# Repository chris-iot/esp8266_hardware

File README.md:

# esp8266_hardware
All layouts and schematics for my ESP8266 based home automation solution

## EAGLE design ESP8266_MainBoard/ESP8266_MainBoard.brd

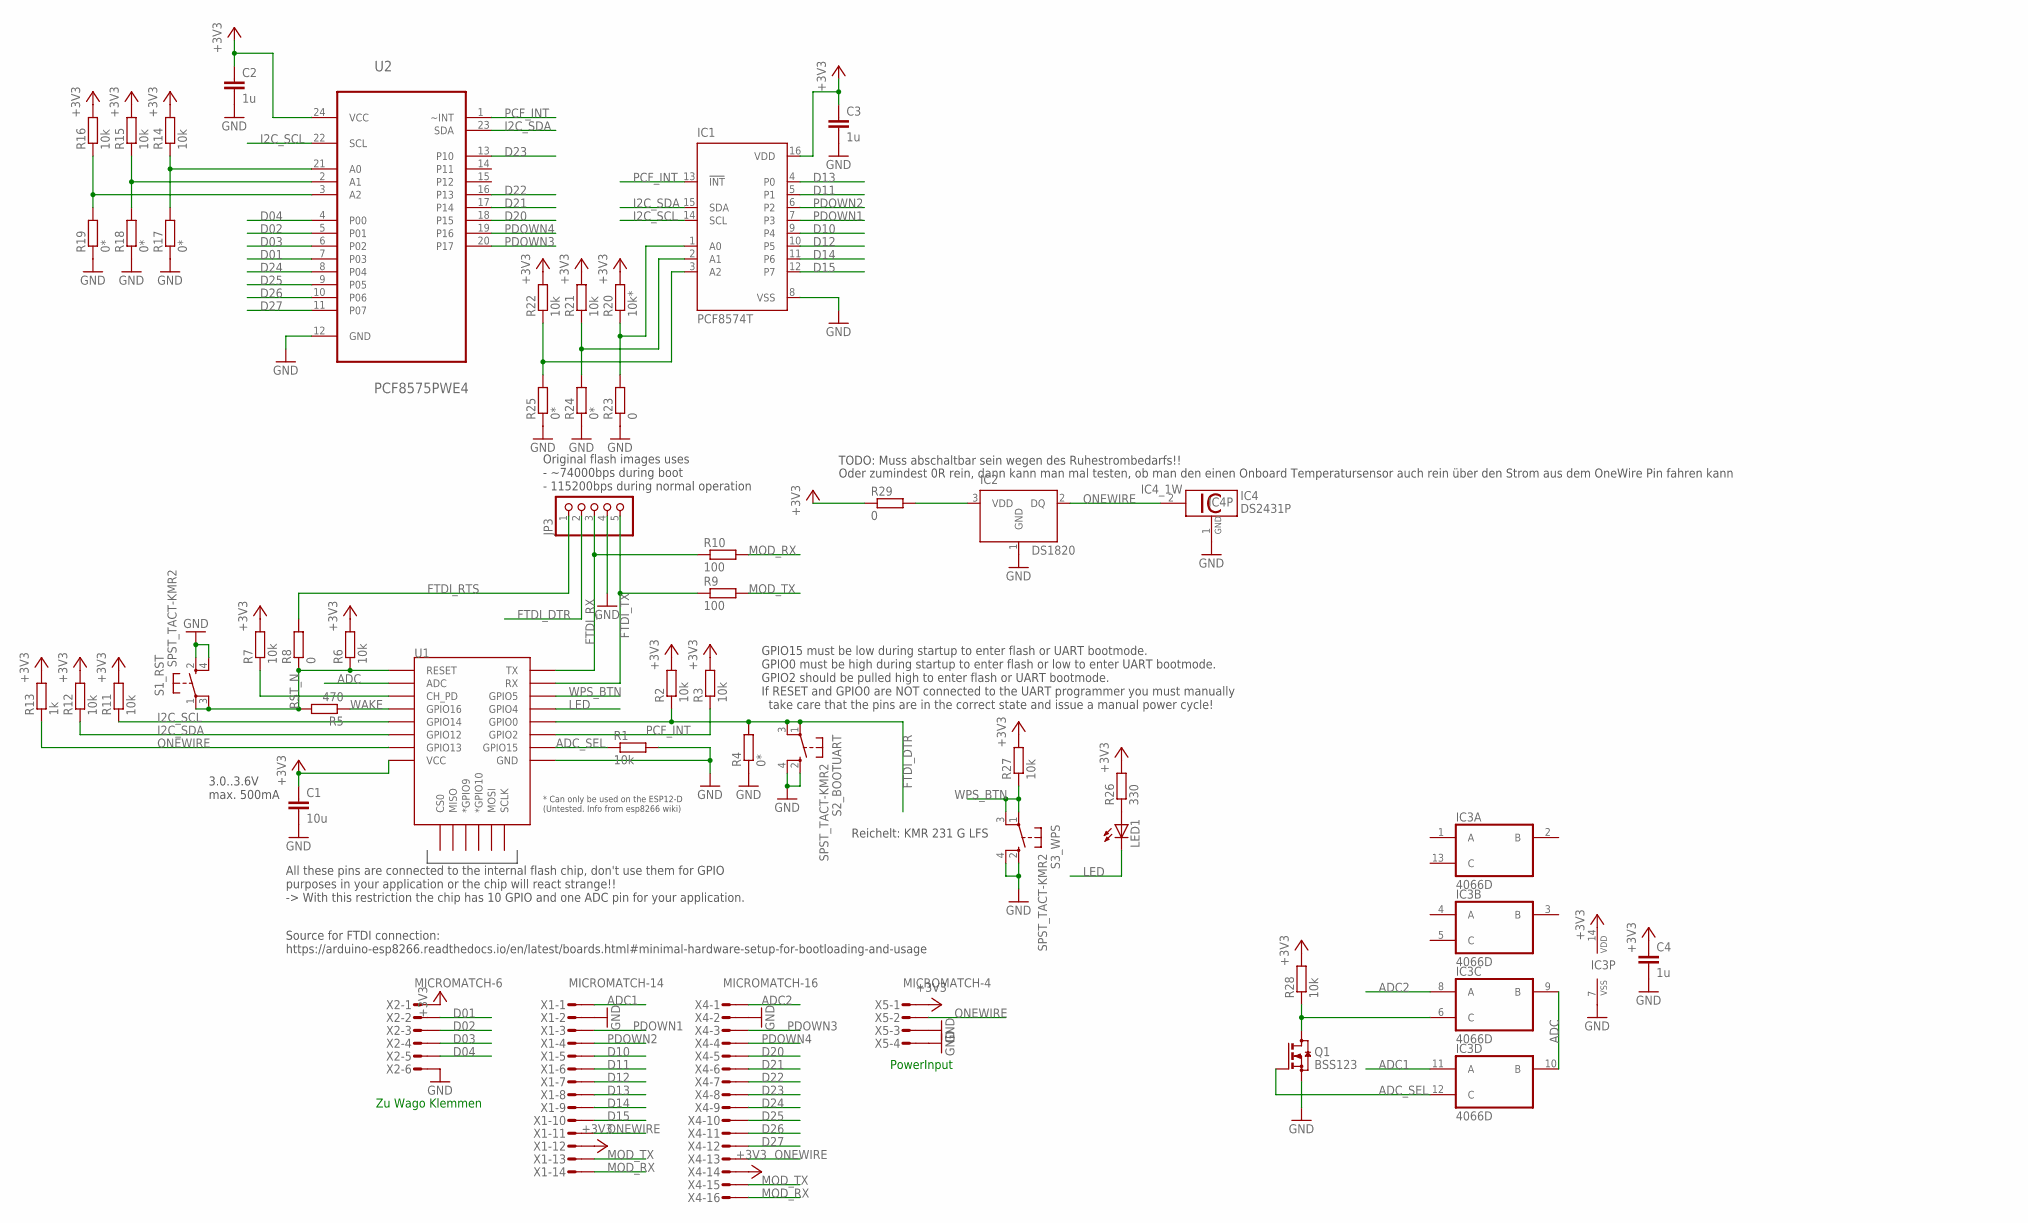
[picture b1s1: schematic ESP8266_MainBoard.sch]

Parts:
C1: 10u; C0805
C2, C3, C4: 1u; C0402
IC1: PCF8574T; SO16W
IC2: DS1820; TO-92
IC3: 4066D; SO14
IC4: DS2431P; TSOC6
JP3: PINHD-1X5; 1X05
LED1: LEDCHIP-LED0603; CHIP-LED0603
Q1: BSS123; SOT23
R1, R2, R3, R6, R7, R11, R12, R14, R15, R16, R21, R22, R27, R28: 10k; R0402
R4, R17, R18, R19, R24, R25: 0*; R0402
R5: 470; R0402
R8, R23, R29: 0; R0402
R9, R10: 100; R0402
R13: 1k; R0402
R20: 10k*; R0402
R26: 330; R0402
S1_RST, S2_BOOTUART, S3_WPS: SPST_TACT-KMR2; KMR2
U1: ESP12ESMD; ESP12E-SMD
U2: PCF8575PWE4; SOP65P640X120-24N
X1: MICROMATCH-14
X2: MICROMATCH-6
X4: MICROMATCH-16
X5: MICROMATCH-4

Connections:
+3V3: C1.1, C2.1, C3.1, C4.1, IC1.16 (VDD), IC3.14 (VDD), R2.2, R3.2, R6.2, R7.2, R11.2, R12.2, R13.2, R14.2, R15.2, R16.2, R20.2, R21.2, R22.2, R26.2, R27.2, R28.2, R29.1, U1.VCC, U2.24 (VCC), X1.12, X2.1, X4.14, X5.1
ADC: IC3.9 (B), IC3.10 (B), U1.ADC
ADC1: IC3.11 (A), X1.1
ADC2: IC3.8 (A), X4.1
ADC_SEL: IC3.12 (C), Q1.1 (G), R1.1, U1.GPIO15
D01: U2.7 (P03), X2.2
D02: U2.5 (P01), X2.3
D03: U2.6 (P02), X2.4
D04: U2.4 (P00), X2.5
D10: IC1.9 (P4), X1.5
D11: IC1.5 (P1), X1.6
D12: IC1.10 (P5), X1.7
D13: IC1.4 (P0), X1.8
D14: IC1.11 (P6), X1.9
D15: IC1.12 (P7), X1.10
D20: U2.18 (P15), X4.5
D21: U2.17 (P14), X4.6
D22: U2.16 (P13), X4.7
D23: U2.13 (P10), X4.8
D24: U2.8 (P04), X4.9
D25: U2.9 (P05), X4.10
D26: U2.10 (P06), X4.11
D27: U2.11 (P07), X4.12
FTDI_DTR: JP3.2, R2.1, R4.2, S2_BOOTUART.1, S2_BOOTUART.3 (P1), U1.GPIO0
FTDI_RTS: JP3.1, R8.2
FTDI_RX: JP3.3, R10.1, U1.TXD0 (TX)
FTDI_TX: JP3.5, R9.1, U1.RXD0 (RX)
GND: C1.2, C2.2, C3.2, C4.2, IC1.8 (VSS), IC2.1 (GND), IC3.7 (VSS), IC4.1 (GND), JP3.4, Q1.2 (S), R1.2, R4.1, R17.1, R18.1, R19.1, R23.1, R24.1, R25.1, S1_RST.2 (S), S1_RST.4 (S1), S2_BOOTUART.2 (S), S2_BOOTUART.4 (S1), S3_WPS.2 (S), S3_WPS.4 (S1), U1.GND, U2.12 (GND), X1.2, X2.6, X4.2, X5.3, X5.4
I2C_SCL: IC1.14 (SCL), R11.1, U1.GPIO14, U2.22 (SCL)
I2C_SDA: IC1.15 (SDA), R12.1, U1.GPIO12, U2.23 (SDA)
LED: LED1.C, U1.GPIO4
MOD_RX: R10.2, X1.14, X4.16
MOD_TX: R9.2, X1.13, X4.15
unnamed: IC3.6 (C), Q1.3 (D), R28.1
unnamed: R14.1, R17.2, U2.21 (A0)
unnamed: R15.1, R18.2, U2.2 (A1)
unnamed: R7.1, U1.CH_PD
unnamed: IC2.3 (VDD), R29.2
unnamed: R16.1, R19.2, U2.3 (A2)
unnamed: IC1.1 (A0), R20.1, R23.2
unnamed: IC1.2 (A1), R21.1, R24.2
unnamed: IC1.3 (A2), R22.1, R25.2
unnamed: LED1.A, R26.1
ONEWIRE: IC2.2 (DQ), IC4.2 (1W), R13.1, U1.GPIO13, X1.11, X4.13, X5.2
PCF_INT: IC1.13 (!INT), R3.1, U1.GPIO2, U2.1 (~INT)
PDOWN1: IC1.7 (P3), X1.3
PDOWN2: IC1.6 (P2), X1.4
PDOWN3: U2.20 (P17), X4.3
PDOWN4: U2.19 (P16), X4.4
RST_N: R5.2, R6.1, R8.1, S1_RST.1, S1_RST.3 (P1), U1.RESET
WAKE: R5.1, U1.GPIO16
WPS_BTN: R27.1, S3_WPS.1, S3_WPS.3 (P1), U1.GPIO5

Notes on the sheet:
3.0..3.6V max. 500mA
GPIO15 must be low during startup to enter flash or UART bootmode. GPIO0 must be high during startup to enter flash or low to enter UART bootmode. GPIO2 should be pulled high to enter flash or UART bootmode. If RESET and GPIO0 are NOT connected to the UART programmer you must manually take care tha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
All these pins are connected to the internal flash chip, don't use them for GPIO purposes in your application or the chip will react strange!! -> With this restriction the chip has 10 GPIO and one ADC pin for your application.
Original flash images uses - ~74000bps during boot - 115200bps during normal operation
Source for FTDI connection: https://arduino-esp8266.readthedocs.io/en/latest/boards.html#minimal-hardware-setup-for-bootloading-and-usage
Zu Wago Klemmen
PowerInput
Reichelt: KMR 231 G LFS
TODO: Muss abschaltbar sein wegen des Ruhestrombedarfs!!
Oder zumindest 0R rein, dann kann man mal testen, ob man den einen Onboard Temperatursensor auch rein über den Strom aus dem OneWire Pin fahren kann

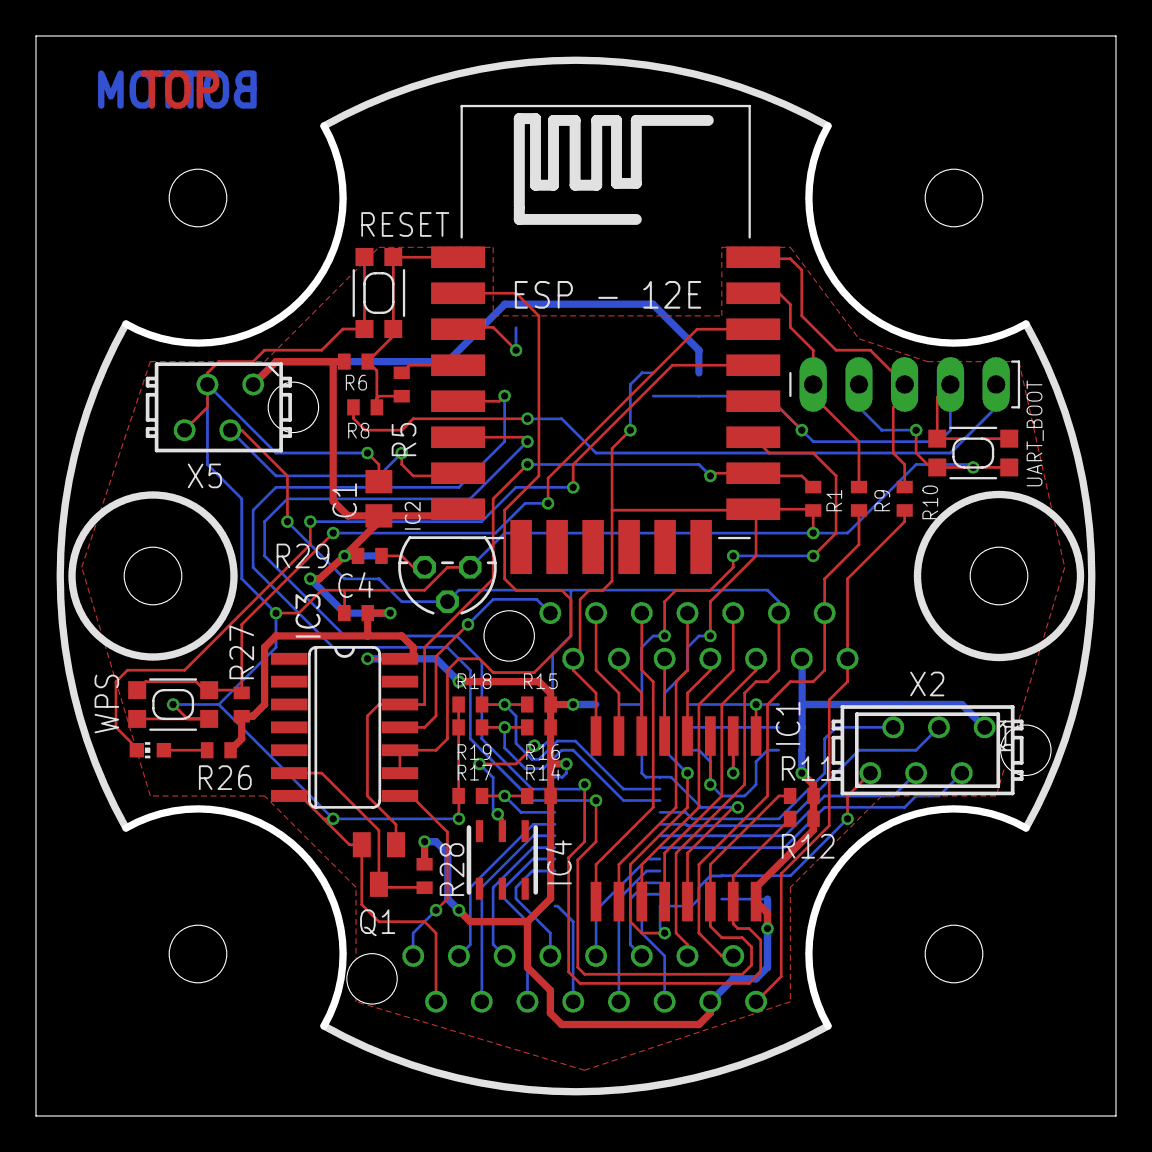
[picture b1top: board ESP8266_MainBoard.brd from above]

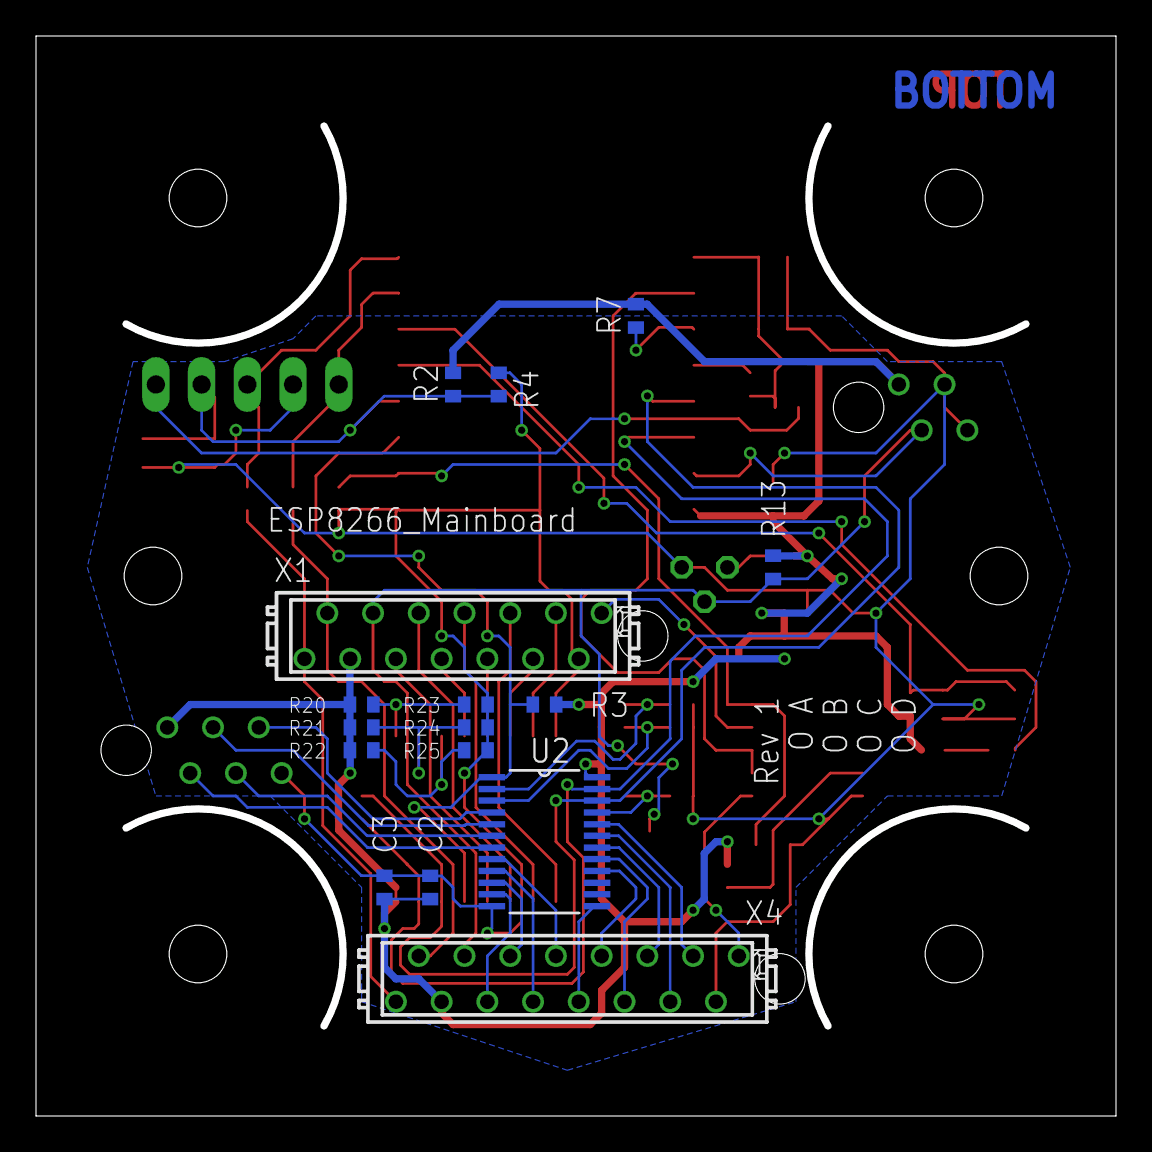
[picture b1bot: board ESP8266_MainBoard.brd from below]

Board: 2 copper layers, 60.0 x 60.0 mm, 49 parts (16 on the bottom side), 52 nets.

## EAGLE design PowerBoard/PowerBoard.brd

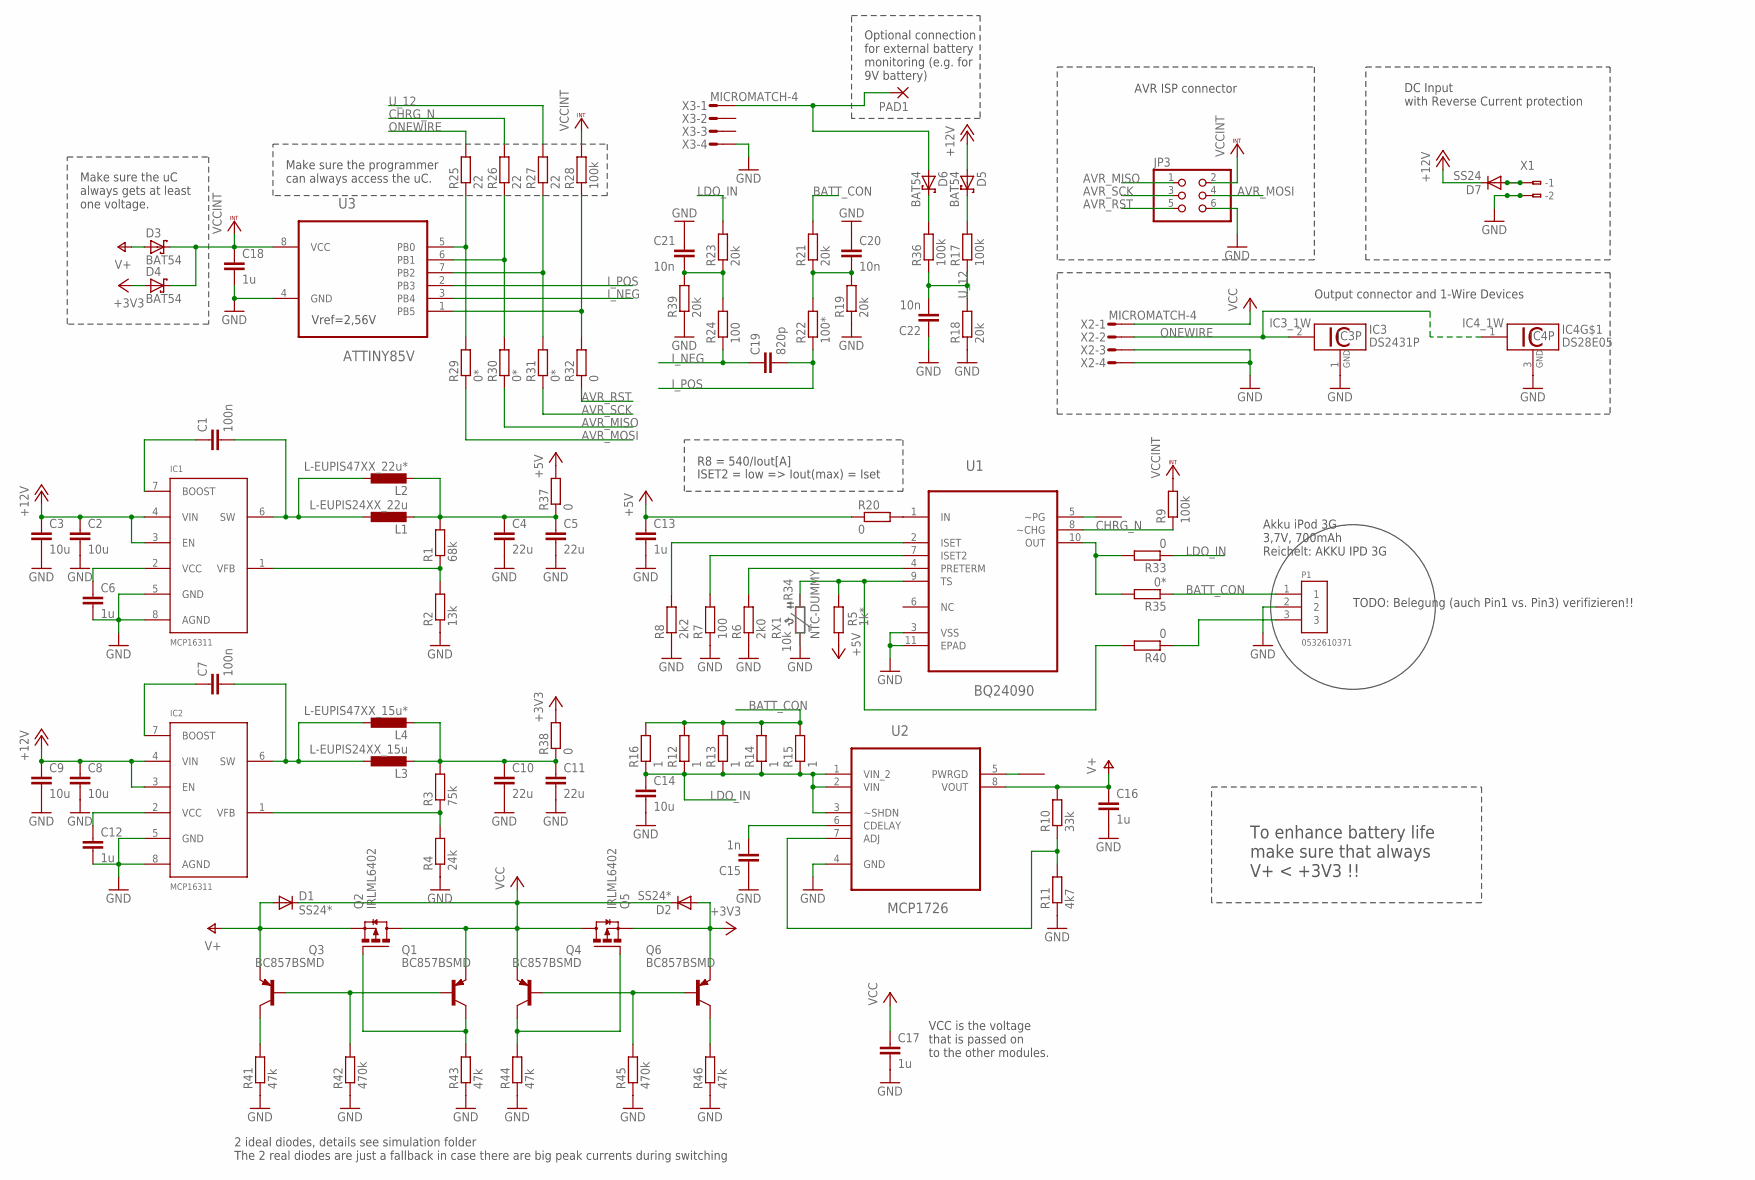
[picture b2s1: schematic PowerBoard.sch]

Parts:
C1, C7: 100n; C0603
C2, C3, C8, C9, C14: 10u; C1210
C4, C5, C10, C11: 22u; C1210
C6, C12, C13, C16, C17, C18: 1u; C0603
C15: 1n; C0603
C19: 820p; C0603
C20, C21, C22: 10n; C0603
D1, D2: SS24*; SMB
D3, D4, D5, D6: BAT54; SOT23
D7: SS24; SMB
IC1, IC2: MCP16311; SOP65P490X110-8N
IC3: DS2431P; TSOC6
IC4: DS28E05; SOT23
JP3: PINHD-2X3; 2X03
L1: L-EUPIS24XX_22u; PIS24XX
L2: L-EUPIS47XX_22u*; PIS47XX
L3: L-EUPIS24XX_15u; PIS24XX
L4: L-EUPIS47XX_15u*; PIS47XX
P1: 0532610371; MOLEX_0532610371
PAD1: WIREPADSMD2,54-5,08; SMD2,54-5,08
Q1, Q3, Q4, Q6: BC857BSMD; SOT23-BEC
Q2, Q5: IRLML6402; SOT23
R1: 68k; R0603
R2: 13k; R0603
R3: 75k; R0603
R4: 24k; R0603
R5: 1k*; R0603
R6: 2k0; R0603
R7, R24: 100; R0603
R8: 2k2; R0603
R9, R17, R36: 100k; R0603
R10: 33k; R0603
R11: 4k7; R0603
R12, R13, R14, R15, R16: 1; R0402
R18, R19, R21, R23, R39: 20k; R0603
R20, R33, R37, R38, R40: 0; R0603
R22: 100*; R0603
R25, R26, R27: 22; R0402
R28: 100k; R0402
R29, R30, R31: 0*; R0402
R32: 0; R0402
R34: 10k; R0603
R35: 0*; R0603
R41, R43, R44, R46: 47k; R0603
R42, R45: 470k; R0603
U1: BQ24090; SOP50P490X110-11N
U2: MCP1726; SOIC127P490X175-8N
U3: ATTINY85V; SOIC127P798X216-8N
U$1, U$3: PAD100-RND; PAD-100-RND
X1: 233-102
X2, X3: MICROMATCH-4

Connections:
+3V3: D2.A, D4.1 (A), Q5.2 (S), Q6.E, R38.2
+5V: C13.1, R5.1, R20.1, R37.2
+12V: C2.1, C3.1, C8.1, C9.1, D5.1 (A), D7.C, IC1.3 (EN), IC1.4 (VIN), IC2.3 (EN), IC2.4 (VIN)
AVR_MISO: JP3.1, R30.1
AVR_MOSI: JP3.4, R29.1
AVR_RST: JP3.5, R32.1
AVR_SCK: JP3.3, R31.1
BATT_CON: P1.1, R12.2, R13.2, R14.2, R15.2, R16.2, R21.2, R35.1
CHRG_N: R9.1, R26.2, U1.8 (~CHG)
GND: C2.2, C3.2, C4.2, C5.2, C6.2, C8.2, C9.2, C10.2, C11.2, C12.2, C13.2, C14.2, C15.1, C16.2, C17.2, C18.2, C20.1, C21.1, C22.1, IC1.5 (GND), IC1.8 (AGND), IC2.5 (GND), IC2.8 (AGND), IC3.1 (GND), IC4.3 (GND), JP3.6, P1.2, R2.1, R4.1, R6.1, R7.1, R8.1, R11.1, R18.1, R19.1, R34.1, R39.1, R41.1, R42.1, R43.1, R44.1, R45.1, R46.1, U1.3 (VSS), U1.11 (EPAD), U2.4 (GND), U3.4 (GND), X1.A2 (-2), X1.B2 (B-2), X2.3, X2.4, X3.4
I_NEG: C19.1, R24.1, U3.3 (PB4)
I_POS: C19.2, R22.1, U3.2 (PB3)
LDO_IN: C14.1, R12.1, R13.1, R14.1, R15.1, R16.1, R23.2, R33.1, U2.1 (VIN_2), U2.2 (VIN), U2.3 (~SHDN)
unnamed: C1.1, IC1.7 (BOOST)
unnamed: C1.2, IC1.6 (SW), L1.2 (1), L2.2 (1)
unnamed: U2.5 (PWRGD), U$3.P$1
unnamed: R8.2, U1.2 (ISET)
unnamed: IC1.1 (VFB), R1.1, R2.2
unnamed: R7.2, U1.7 (ISET2)
unnamed: C6.1, IC1.2 (VCC)
unnamed: R6.2, U1.4 (PRETERM)
unnamed: C7.1, IC2.7 (BOOST)
unnamed: C7.2, IC2.6 (SW), L3.2 (1), L4.2 (1)
unnamed: IC2.1 (VFB), R3.1, R4.2
unnamed: C12.1, IC2.2 (VCC)
unnamed: R5.2, R34.2, R40.2, U1.9 (TS)
unnamed: U1.5 (~PG), U$1.P$1
unnamed: C15.2, U2.6 (CDELAY)
unnamed: R28.1, R32.2, U3.1 (PB5)
unnamed: D6.3 (C), R36.2
unnamed: R27.1, R31.2, U3.7 (PB2)
unnamed: R26.1, R30.2, U3.6 (PB1)
unnamed: R10.1, R11.2, U2.7 (ADJ)
unnamed: C21.2, R23.1, R24.2, R39.2
unnamed: D7.A, X1.A1 (-1), X1.B1 (B-1)
unnamed: R25.1, R29.2, U3.5 (PB0)
unnamed: D6.1 (A), PAD1.1, X3.1
unnamed: C4.1, C5.1, L1.1 (2), L2.1 (2), R1.2, R37.1
unnamed: C10.1, C11.1, L3.1 (2), L4.1 (2), R3.2, R38.1
unnamed: C20.2, R19.2, R21.1, R22.2
unnamed: D5.3 (C), R17.2
unnamed: R20.2, U1.1 (IN)
unnamed: R33.2, R35.2, U1.10 (OUT)
unnamed: P1.3, R40.1
unnamed: Q1.C, Q2.1 (G), R43.2
unnamed: Q1.B, Q3.B, R42.2
unnamed: Q3.C, R41.2
unnamed: Q4.C, Q5.1 (G), R44.2
unnamed: Q4.B, Q6.B, R45.2
unnamed: Q6.C, R46.2
ONEWIRE: IC3.2 (1W), IC4.1 (1W), R25.2, X2.2
U_12: C22.2, R17.1, R18.2, R27.2, R36.1
V+: C16.1, D1.A, D3.1 (A), Q2.2 (S), Q3.E, R10.2, U2.8 (VOUT)
VCC: C17.1, D1.C, D2.C, Q1.E, Q2.3 (D), Q4.E, Q5.3 (D), X2.1
VCCINT: C18.1, D3.3 (C), D4.3 (C), JP3.2, R9.2, R28.2, U3.8 (VCC)

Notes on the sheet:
VCC is the voltage that is passed on to the other modules.
Optional connection for external battery monitoring (e.g. for 9V battery)
Akku iPod 3G 3,7V, 700mAh Reichelt: AKKU IPD 3G
R8 = 540/Iout[A]
To enhance battery life make sure that always V+ < +3V3 !!
ISET2 = low => Iout(max) = Iset
Vref=2,56V
TODO: Belegung (auch Pin1 vs. Pin3) verifizieren!!
Make sure the uC always gets at least one voltage.
Make sure the programmer can always access the uC.
AVR ISP connector
DC Input with Reverse Current protection
Output connector and 1-Wire Devices
2 ideal diodes, details see simulation folder The 2 real diodes are just a fallback in case there are big peak currents during switching

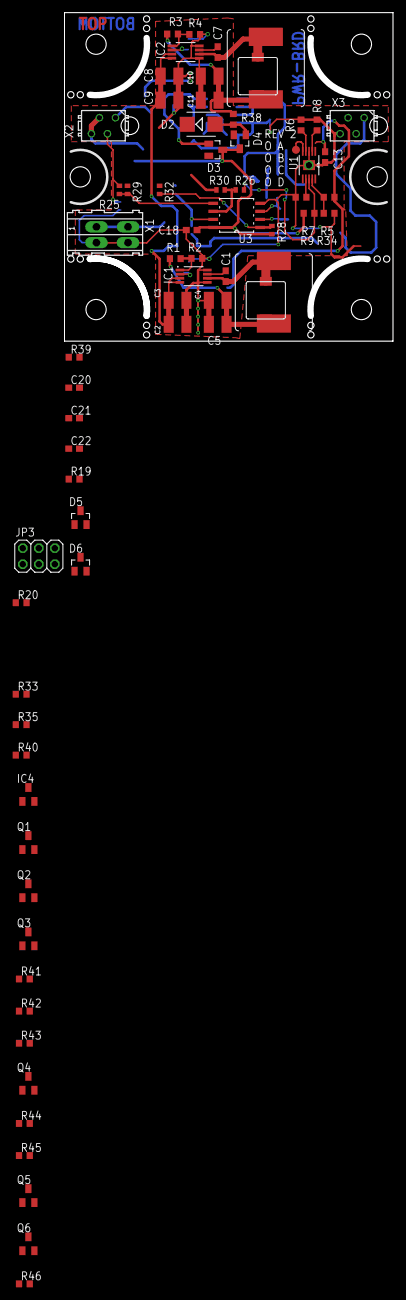
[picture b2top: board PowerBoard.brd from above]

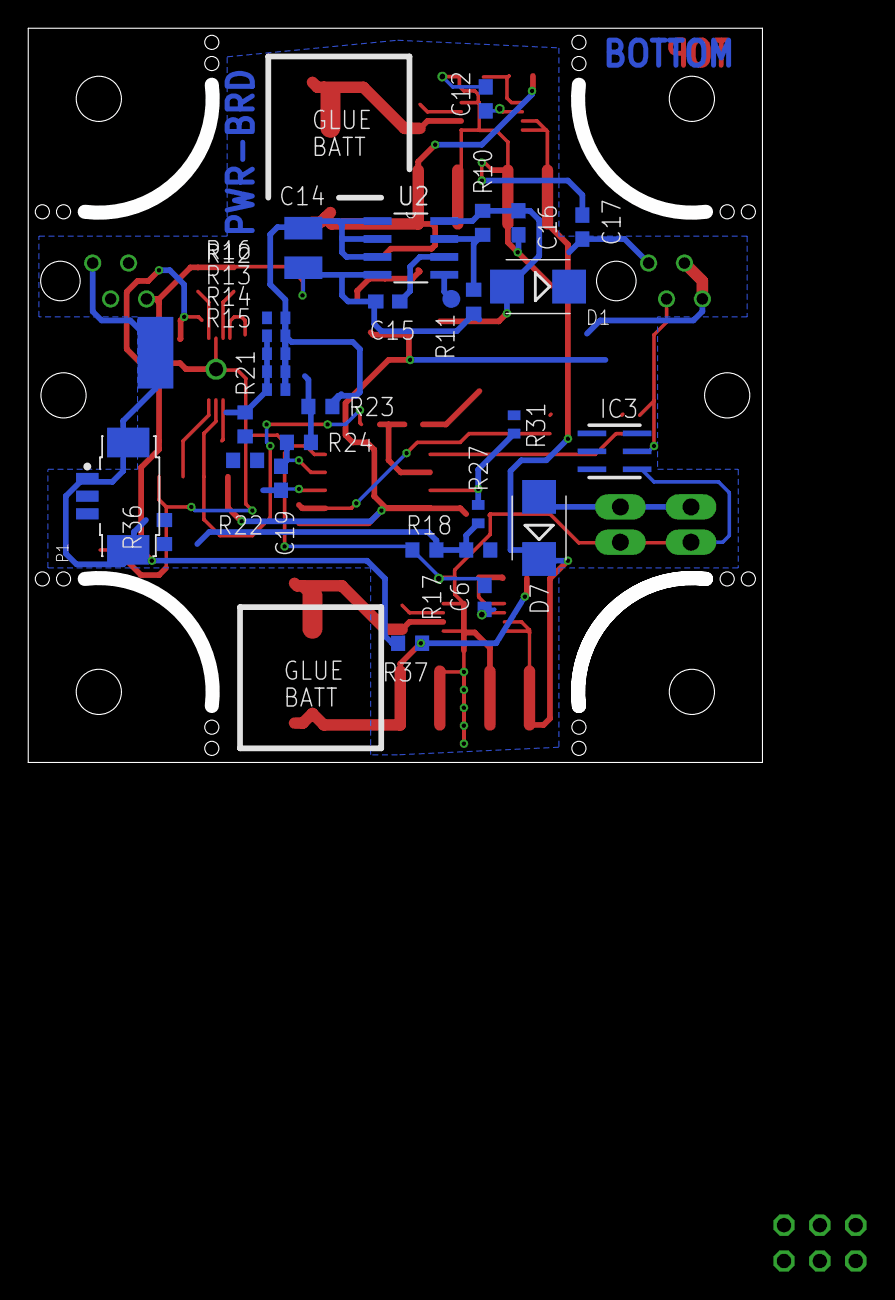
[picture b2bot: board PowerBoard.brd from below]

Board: 2 copper layers, 52.0 x 52.0 mm, 100 parts (31 on the bottom side), 55 nets.

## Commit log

2018-01-21 Initial commit of the state that has been produced up to now
2018-01-21 Create LICENSE
2018-01-21 Added all inputs from the bringup phase of Rev0
2018-01-21 Added inputs for Rev2 of PowerBoard to schematic
2018-01-21 Little directory structure cleanup
2018-01-21 Further cleanups
2018-01-21 Cleaning up
2018-01-21 Again Cleanup
2018-01-21 Optical cleanup of the schematic, added ideal diodes and some other stuff from the TODO list
2018-09-03 R13 von 4k7 nach 1k
